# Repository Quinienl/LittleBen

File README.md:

# LittleBen
 LittleBen eurorack master clock

LittleBen is a masterclock for eurorack. It's based on a Arduino Mini. This is the second version. I decided to open source all files for this module. In this repo you will find all the files needed for making the pcb and panel for littleben. This files are created with Kicad 6.

This version has a few minor issues I would like to fix. 
- The panel has a hole for the lcd screen thats need a little bit more on the left side and a little less on the right side.

More info at:
https://www.quinie.nl/category/diy/littleben/

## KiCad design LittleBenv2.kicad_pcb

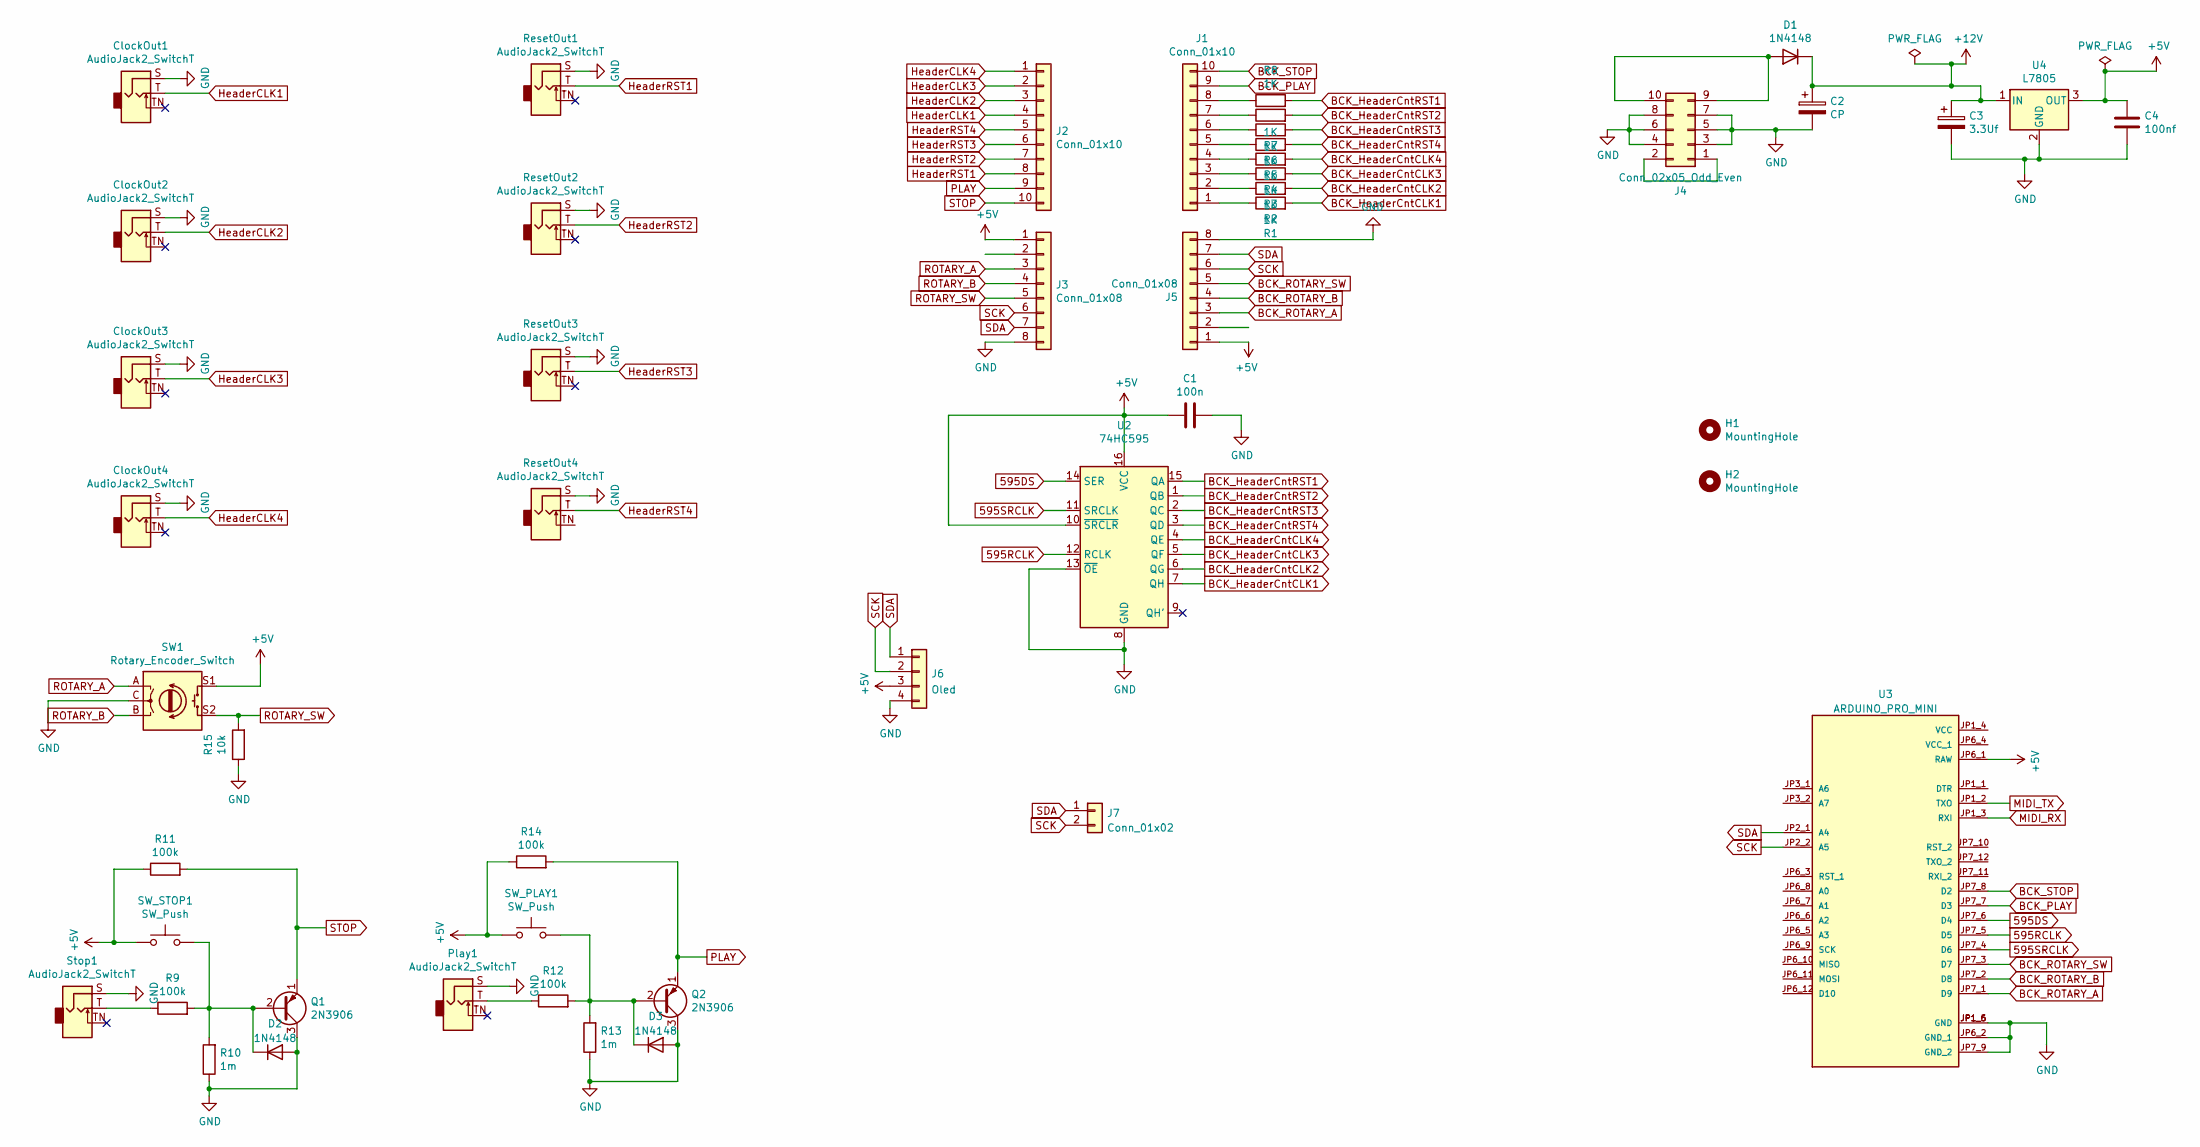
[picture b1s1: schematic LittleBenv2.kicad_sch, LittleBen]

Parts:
C1: 100n; C_Disc_D5.0mm_W2.5mm_P5.00mm
C2: CP; CP_Radial_D6.3mm_P2.50mm
C3: 3.3Uf; CP_Radial_D6.3mm_P2.50mm
C4: 100nf; C_Disc_D5.0mm_W2.5mm_P5.00mm
ClockOut1, ClockOut2, ClockOut3, ClockOut4: AudioJack2_SwitchT; Jack_3.5mm_QingPu_WQP-PJ398SM_Vertical_CircularHoles
D1, D2, D3: 1N4148; D_DO-35_SOD27_P7.62mm_Horizontal
H1, H2: MountingHole; MountingHole_3mm
J1: Conn_01x10; PinHeader_1x10_P2.54mm_Vertical
J2: Conn_01x10; PinSocket_1x10_P2.54mm_Vertical
J3: Conn_01x08; PinSocket_1x08_P2.54mm_Vertical
J4: Conn_02x05_Odd_Even; IDC-Header_2x05_P2.54mm_Vertical
J5: Conn_01x08; PinHeader_1x08_P2.54mm_Vertical
J6: Oled; PinHeader_1x04_P2.54mm_Vertical
J7: Conn_01x02; PinHeader_1x02_P2.54mm_Vertical
Play1: AudioJack2_SwitchT; Jack_3.5mm_QingPu_WQP-PJ398SM_Vertical_CircularHoles
Q1, Q2: 2N3906; TO-92_Inline_Wide
R1, R2, R3, R4, R5, R6, R7, R8: 1K; R_Axial_DIN0207_L6.3mm_D2.5mm_P10.16mm_Horizontal
R9, R11, R12, R14: 100k; R_Axial_DIN0207_L6.3mm_D2.5mm_P10.16mm_Horizontal
R10, R13: 1m; R_Axial_DIN0207_L6.3mm_D2.5mm_P10.16mm_Horizontal
R15: 10k; R_Axial_DIN0207_L6.3mm_D2.5mm_P10.16mm_Horizontal
ResetOut1, ResetOut2, ResetOut3, ResetOut4: AudioJack2_SwitchT; Jack_3.5mm_QingPu_WQP-PJ398SM_Vertical_CircularHoles
SW1: Rotary_Encoder_Switch; RotaryEncoder_Alps_EC12E-Switch_Vertical_H20mm
SW_PLAY1: SW_Push; TL2230
SW_STOP1: SW_Push; TL2230
Stop1: AudioJack2_SwitchT; Jack_3.5mm_QingPu_WQP-PJ398SM_Vertical_CircularHoles
U2: 74HC595; DIP-16_W7.62mm
U3: ARDUINO_PRO_MINI; MODULE_ARDUINO_PRO_MINI; PARTREV N/A
U4: L7805; TO-220-3_Vertical

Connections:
595DS: U2.14 (SER), U3.JP7_6 (D4)
595RCLK: U2.12 (RCLK), U3.JP7_5 (D5)
595SRCLK: U2.11 (SRCLK), U3.JP7_4 (D6)
+5V: C1.2, C4.1, J3.1, J5.1, J6.3, R11.1, R14.1, SW1.S1, SW_PLAY1.1, SW_STOP1.1, U2.10 (~SRCLR), U2.16 (VCC), U3.JP6_1 (RAW), U4.3 (OUT)
+12V: C2.1, C3.1, D1.1 (K), U4.1 (IN)
BCK_HeaderCntCLK1: R1.2, U2.7 (QH)
BCK_HeaderCntCLK2: R2.2, U2.6 (QG)
BCK_HeaderCntCLK3: R3.2, U2.5 (QF)
BCK_HeaderCntCLK4: R4.2, U2.4 (QE)
BCK_HeaderCntRST1: R8.2, U2.15 (QA)
BCK_HeaderCntRST2: R7.2, U2.1 (QB)
BCK_HeaderCntRST3: R6.2, U2.2 (QC)
BCK_HeaderCntRST4: R5.2, U2.3 (QD)
BCK_PLAY: J1.9, U3.JP7_7 (D3)
BCK_ROTARY_A: J5.3, U3.JP7_1 (D9)
BCK_ROTARY_B: J5.4, U3.JP7_2 (D8)
BCK_ROTARY_SW: J5.5, U3.JP7_3 (D7)
BCK_STOP: J1.10, U3.JP7_8 (D2)
GND: C1.1, C2.2, C3.2, C4.2, ClockOut1.S, ClockOut2.S, ClockOut3.S, ClockOut4.S, D2.2 (A), D3.2 (A), J3.8, J4.3, J4.4, J4.5, J4.6, J4.7, J4.8, J5.8, J6.4, Play1.S, Q1.3 (C), Q2.3 (C), R10.1, R13.1, R15.1, ResetOut1.S, ResetOut2.S, ResetOut3.S, ResetOut4.S, SW1.C, Stop1.S, U2.8 (GND), U2.13 (~OE), U3.JP1_5 (GND), U3.JP1_6 (GND), U3.JP6_2 (GND_1), U3.JP7_9 (GND_2), U4.2 (GND)
HeaderCLK1: ClockOut1.T, J2.4
HeaderCLK2: ClockOut2.T, J2.3
HeaderCLK3: ClockOut3.T, J2.2
HeaderCLK4: ClockOut4.T, J2.1
HeaderRST1: J2.8, ResetOut1.T
HeaderRST2: J2.7, ResetOut2.T
HeaderRST3: J2.6, ResetOut3.T
HeaderRST4: J2.5, ResetOut4.T
MIDI_RX: U3.JP1_3 (RXI)
MIDI_TX: U3.JP1_2 (TXO)
unnamed: D1.2 (A), J4.9, J4.10
unnamed: J1.1, R1.1
unnamed: J1.2, R2.1
unnamed: J1.3, R3.1
unnamed: J1.4, R4.1
unnamed: J1.5, R5.1
unnamed: J1.6, R6.1
unnamed: J1.7, R7.1
unnamed: J1.8, R8.1
unnamed: J4.1, J4.2
unnamed: Play1.T, R12.1
unnamed: D2.1 (K), Q1.2 (B), R9.2, R10.2, SW_STOP1.2
unnamed: D3.1 (K), Q2.2 (B), R12.2, R13.2, SW_PLAY1.2
unnamed: R9.1, Stop1.T
PLAY: J2.9, Q2.1 (E), R14.2
ROTARY_A: J3.3, SW1.A
ROTARY_B: J3.4, SW1.B
ROTARY_SW: J3.5, R15.2, SW1.S2
SCK: J3.6, J5.6, J6.2, J7.2, U3.JP2_2 (A5)
SDA: J3.7, J5.7, J6.1, J7.1, U3.JP2_1 (A4)
STOP: J2.10, Q1.1 (E), R11.2

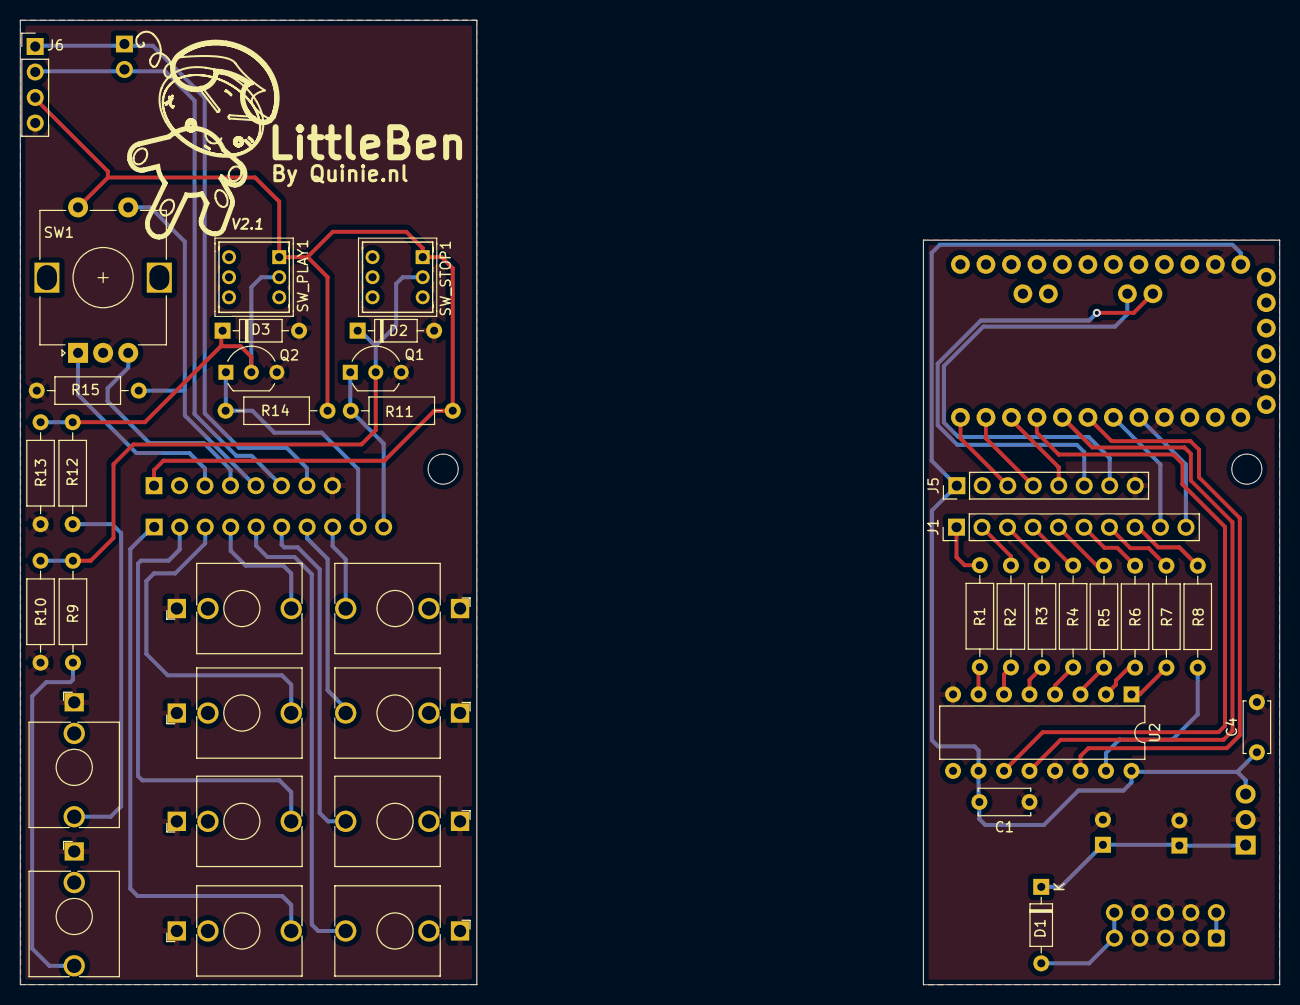
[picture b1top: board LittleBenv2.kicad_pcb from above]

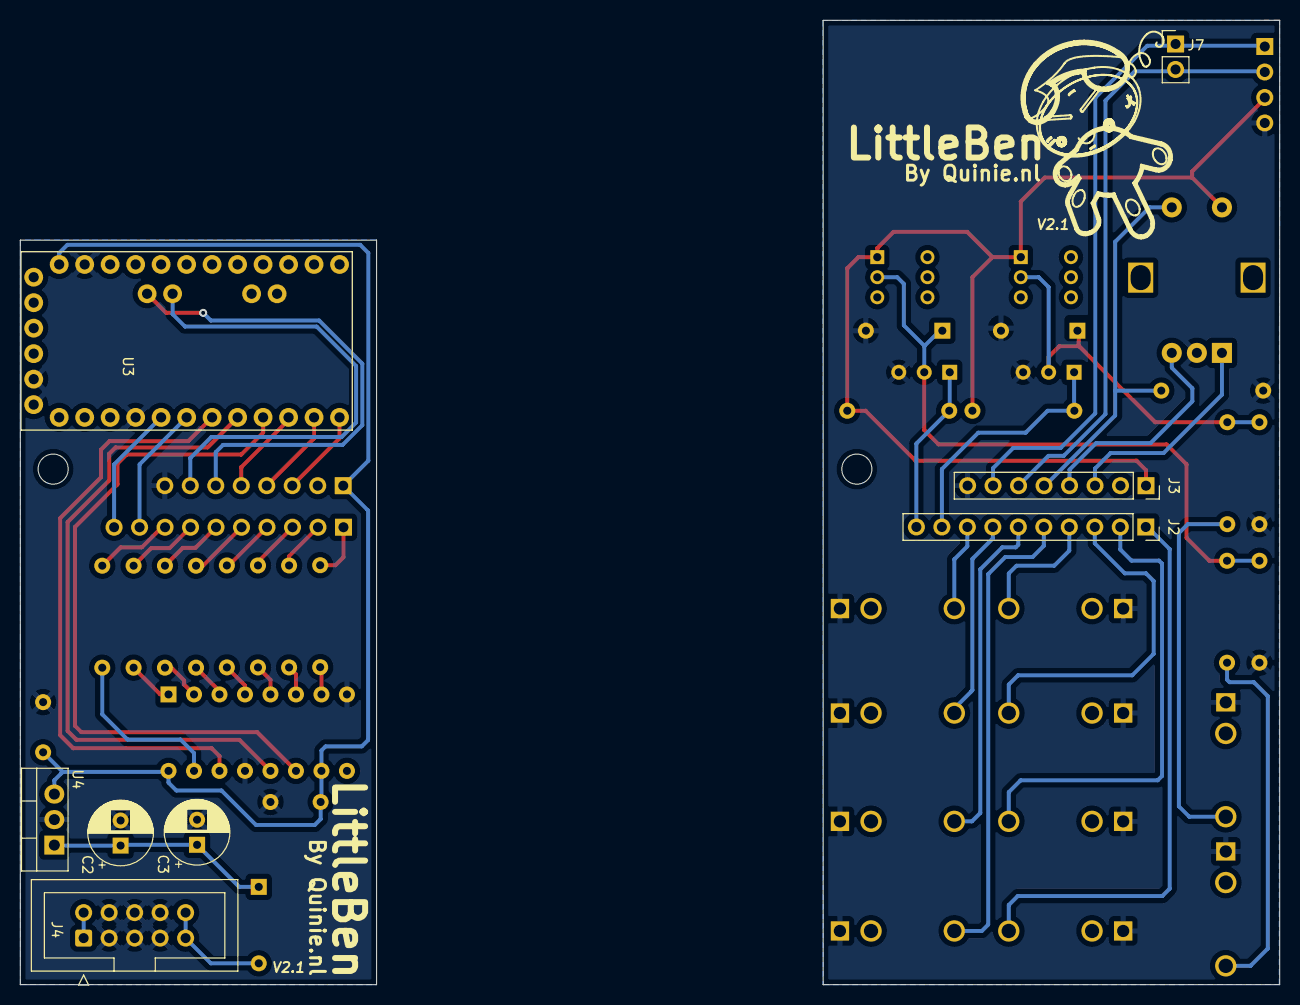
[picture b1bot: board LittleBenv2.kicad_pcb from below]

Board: 2 copper layers, 125.5 x 96.1 mm, 49 parts (8 on the bottom side), 48 nets.

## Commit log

2022-11-12 Opensourcing Littleben
    First upload
2022-11-12 picture
2022-11-18 Panel Update
2022-12-12 Clean Folders
